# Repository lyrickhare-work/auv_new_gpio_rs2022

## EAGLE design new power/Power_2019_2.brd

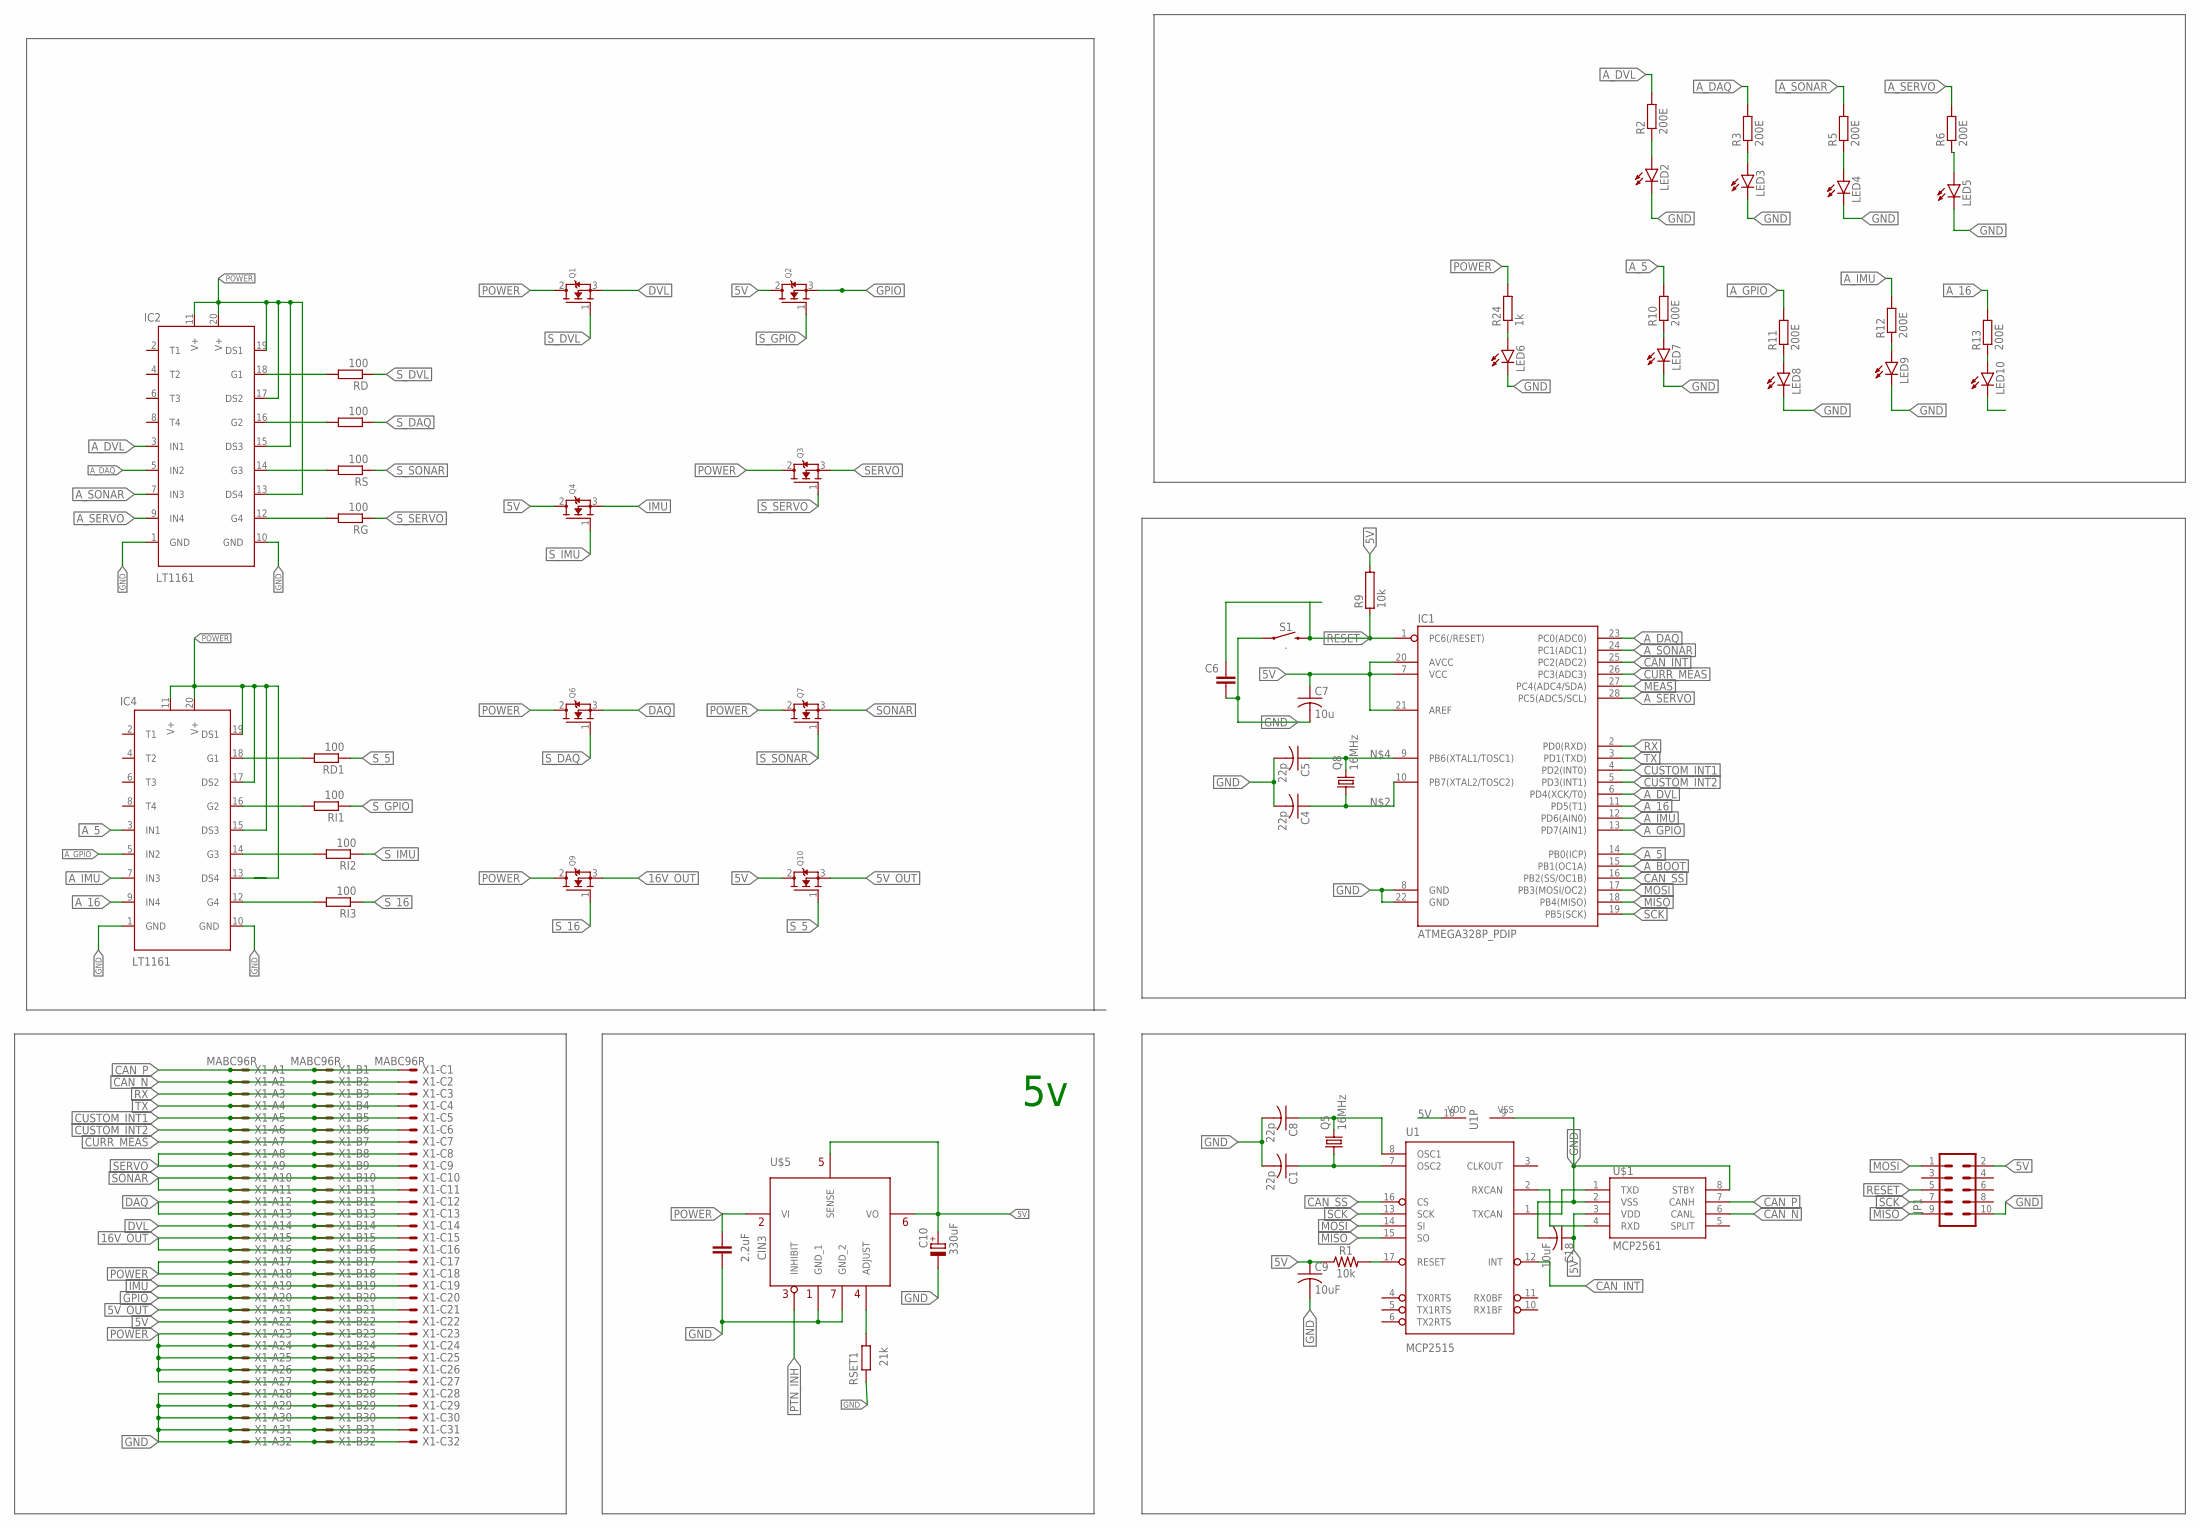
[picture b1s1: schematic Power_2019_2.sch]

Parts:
C1, C4, C5, C8: 22p; C025-024X044
C6: C-EU025-050X050; C025-050X050
C7: 10u; C025-050X050
C9, C18: 10uF; C025-050X050
C10: 330uF; E2,5-5
CIN3: 2.2uF; C0805
IC1: ATMEGA328P_PDIP; DIL28-3
IC2, IC4: LT1161; ROBOSUB_LINEAR-TECHNOLOGY_LT1161_QUAD-HIGH-SIDE-MOSFET-DRIV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
JP1: CONN_05X2SHD; 2X5-SHROUDED
LED2, LED3, LED4, LED5, LED6, LED7, LED8, LED9, LED10: LEDCHIPLED_0805; CHIPLED_0805
Q1, Q2, Q3, Q4, Q6, Q7, Q9, Q10: MOSFET-NGDS_TO220V; TO220V
Q5, Q8: 16MHz; HC49/S
R1: 10k; AXIAL-0.3
R2, R3, R5, R6, R10, R11, R12, R13: 200E; M0805
R9: 10k; RS1/4
R24: 1k; M0805
RD, RD1: 100; M0805
RG: 100; M0805
RI, RI1, RI2, RI3: 100; M0805
RS: 100; M0805
RSET1: 21k; M0805
S1: .; TACTILE_SWITCH_PTH_6.0MM
U1: MCP2515; DIP18
U$1: MCP2561; DIP08
U$5: PTN78060WAH
X1: MABC96R

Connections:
5V: C7.1, C9.1, C10.+, C18.1, IC1.7 (VCC), IC1.20 (AVCC), IC1.21 (AREF), JP1.2, Q2.2 (D), Q4.2 (D), Q10.2 (D), R1.P$1 (1), R9.2, U1.18 (VDD), U$1.3 (VDD), U$5.5 (SENSE), U$5.6 (VO), X1.A22, X1.B22, X1.C22
5V_OUT: Q10.3 (S), X1.A21, X1.B21, X1.C21
16V_OUT: Q9.3 (S), X1.A15, X1.A16, X1.B15, X1.B16, X1.C15, X1.C16
A_5: IC1.14 (PB0(ICP)), IC4.3 (IN1), R10.2
A_16: IC1.11 (PD5(T1)), IC4.9 (IN4), R13.2
A_BOOT: IC1.15 (PB1(OC1A))
A_DAQ: IC1.23 (PC0(ADC0)), IC2.5 (IN2), R3.2
A_DVL: IC1.6 (PD4(XCK/T0)), IC2.3 (IN1), R2.2
A_GPIO: IC1.13 (PD7(AIN1)), IC4.5 (IN2), R11.2
A_IMU: IC1.12 (PD6(AIN0)), IC4.7 (IN3), R12.2
A_SERVO: IC1.28 (PC5(ADC5/SCL)), IC2.9 (IN4), R6.2
A_SONAR: IC1.24 (PC1(ADC1)), IC2.7 (IN3), R5.2
CAN_INT: IC1.25 (PC2(ADC2)), U1.12 (INT)
CAN_N: U$1.6 (CANL), X1.A2, X1.B2, X1.C2
CAN_P: U$1.7 (CANH), X1.A1, X1.B1, X1.C1
CAN_SS: IC1.16 (PB2(SS/OC1B)), U1.16 (CS)
CURR_MEAS: IC1.26 (PC3(ADC3)), X1.A7, X1.B7, X1.C7
CUSTOM_INT1: IC1.4 (PD2(INT0)), X1.A5, X1.B5, X1.C5
CUSTOM_INT2: IC1.5 (PD3(INT1)), X1.A6, X1.B6, X1.C6
D: IC2.12 (G4), RG.2
DAQ: Q6.3 (S), X1.A12, X1.A13, X1.B12, X1.B13, X1.C12, X1.C13
DVL: Q1.3 (S), X1.A14, X1.B14, X1.C14
G: IC2.18 (G1), RD.2
G1: IC4.18 (G1), RD1.2
GND: C1.2, C4.2, C5.2, C6.2, C7.2, C8.2, C9.2, C10.-, C18.2, CIN3.1, IC1.8 (GND), IC1.22 (GND), IC2.1 (GND), IC2.10 (GND), IC4.1 (GND), IC4.10 (GND), JP1.10, LED2.C, LED3.C, LED4.C, LED5.C, LED6.C, LED7.C, LED8.C, LED9.C, LED10.C, RSET1.2, S1.1, U1.9 (VSS), U$1.2 (VSS), U$1.8 (STBY), U$5.1 (GND_1), U$5.7 (GND_2), X1.A28, X1.A29, X1.A30, X1.A31, X1.A32, X1.B28, X1.B29, X1.B30, X1.B31, X1.B32, X1.C28, X1.C29, X1.C30, X1.C31, X1.C32
GPIO: Q2.3 (S), X1.A20, X1.B20, X1.C20
I: IC2.14 (G3), RS.2
IMU: Q4.3 (S), X1.A19, X1.B19, X1.C19
MEAS: IC1.27 (PC4(ADC4/SDA))
MISO: IC1.18 (PB4(MISO)), JP1.9, U1.15 (SO)
MOSI: IC1.17 (PB3(MOSI/OC2)), JP1.1, U1.14 (SI)
unnamed: LED2.A, R2.1
unnamed: C4.1, IC1.10 (PB7(XTAL2/TOSC2)), Q8.1
unnamed: U1.1 (TXCAN), U$1.1 (TXD)
unnamed: C5.1, IC1.9 (PB6(XTAL1/TOSC1)), Q8.2
unnamed: LED3.A, R3.1
unnamed: U1.2 (RXCAN), U$1.4 (RXD)
unnamed: R1.P$2 (2), U1.17 (RESET)
unnamed: C1.1, Q5.1, U1.7 (OSC2)
unnamed: C8.1, Q5.2, U1.8 (OSC1)
unnamed: RSET1.1, U$5.4 (ADJUST)
unnamed: LED4.A, R5.1
unnamed: LED5.A, R6.1
unnamed: LED7.A, R10.1
unnamed: LED6.A, R24.1
unnamed: LED8.A, R11.1
unnamed: LED9.A, R12.1
unnamed: LED10.A, R13.1
unnamed: IC4.14 (G3), RI2.2
unnamed: IC4.12 (G4), RI3.2
POWER: CIN3.2, IC2.11 (V+), IC2.13 (DS4), IC2.15 (DS3), IC2.17 (DS2), IC2.19 (DS1), IC2.20 (V+), IC4.11 (V+), IC4.13 (DS4), IC4.15 (DS3), IC4.17 (DS2), IC4.19 (DS1), IC4.20 (V+), Q1.2 (D), Q3.2 (D), Q6.2 (D), Q7.2 (D), Q9.2 (D), R24.2, U$5.2 (VI), X1.A17, X1.A18, X1.A23, X1.A24, X1.A25, X1.A26, X1.A27, X1.B17, X1.B18, X1.B23, X1.B24, X1.B25, X1.B26, X1.B27, X1.C17, X1.C18, X1.C23, X1.C24, X1.C25, X1.C26, X1.C27
PTN_INH: U$5.3 (INHIBIT)
RESET: C6.1, IC1.1 (PC6(/RESET)), JP1.5, R9.1, S1.3 (2)
RX: IC1.2 (PD0(RXD)), X1.A3, X1.B3, X1.C3
S: IC2.16 (G2), RI.2
S1: IC4.16 (G2), RI1.2
SCK: IC1.19 (PB5(SCK)), JP1.7, U1.13 (SCK)
SERVO: Q3.3 (S), X1.A8, X1.A9, X1.B8, X1.B9, X1.C8, X1.C9
SONAR: Q7.3 (S), X1.A10, X1.A11, X1.B10, X1.B11, X1.C10, X1.C11
S_5: Q10.1 (G), RD1.1
S_16: Q9.1 (G), RI3.1
S_DAQ: Q6.1 (G), RI.1
S_DVL: Q1.1 (G), RD.1
S_GPIO: Q2.1 (G), RI1.1
S_IMU: Q4.1 (G), RI2.1
S_SERVO: Q3.1 (G), RG.1
S_SONAR: Q7.1 (G), RS.1
TX: IC1.3 (PD1(TXD)), X1.A4, X1.B4, X1.C4

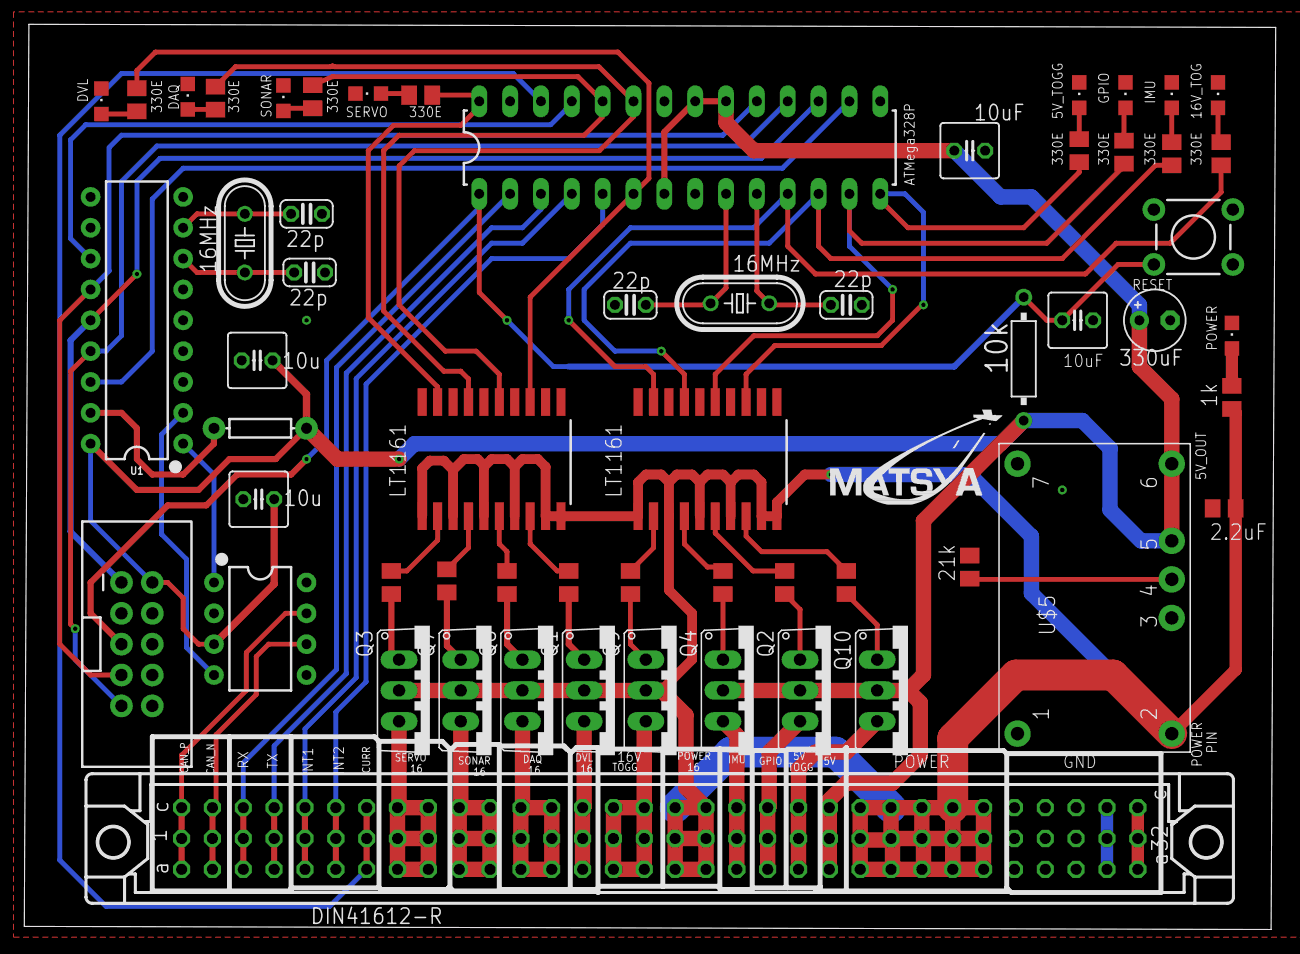
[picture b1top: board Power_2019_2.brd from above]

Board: 2 copper layers, 103.0 x 74.5 mm, 58 parts (0 on the bottom side), 65 nets.

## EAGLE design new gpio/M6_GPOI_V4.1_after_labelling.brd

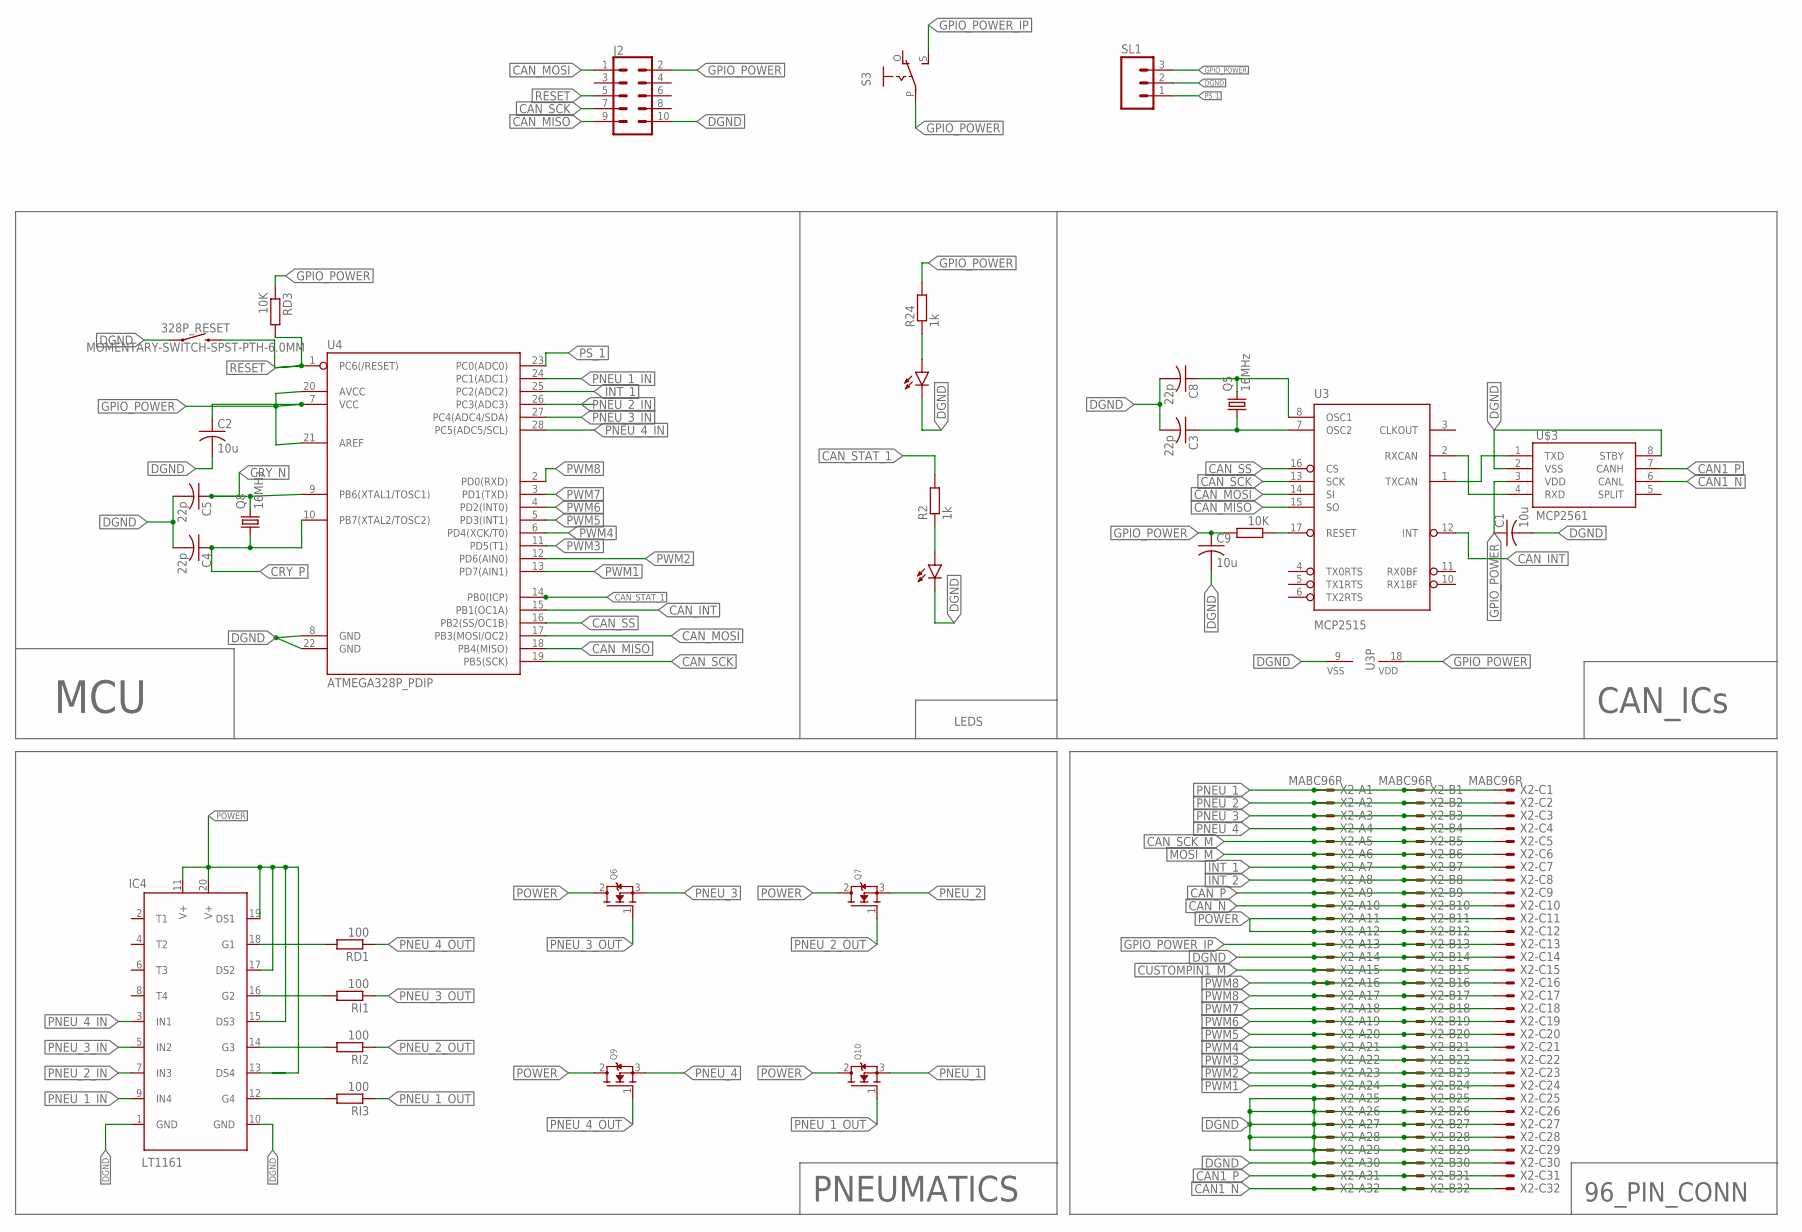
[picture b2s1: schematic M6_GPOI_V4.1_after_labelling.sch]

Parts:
328P_RESET: MOMENTARY-SWITCH-SPST-PTH-6.0MM; TACTILE_SWITCH_PTH_6.0MM
C1, C2, C9: 10u; C025-050X050
C3, C4, C5, C8: 22p; C025-024X044
IC4: LT1161; ROBOSUB_LINEAR-TECHNOLOGY_LT1161_QUAD-HIGH-SIDE-MOSFET-DRIV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
J2: CONN_05X2SHD; 2X5-SHROUDED
PWR, PWR1: LED5MM
Q5, Q8: 16MHz; HC49/S
Q6, Q7, Q9, Q10: MOSFET-NGDS_TO220V; TO220V
R2, R24: 1k; M0805
RD1: 100; M0805
RD2, RD3: 10K; M0805
RI1, RI2, RI3: 100; M0805
S3: EG1218S; EG1218
SL1: MA03; 03P
U3: MCP2515; DIP18
U4: ATMEGA328P_PDIP; DIL28-3
U$3: MCP2561; DIP08
X2: MABC96R

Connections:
CAN1_N: U$3.6 (CANL), X2.A32, X2.B32, X2.C32
CAN1_P: U$3.7 (CANH), X2.A31, X2.B31, X2.C31
CAN_INT: U3.12 (INT), U4.15 (PB1(OC1A))
CAN_MISO: J2.9, U3.15 (SO), U4.18 (PB4(MISO))
CAN_MOSI: J2.1, U3.14 (SI), U4.17 (PB3(MOSI/OC2))
CAN_N: X2.A10, X2.B10, X2.C10
CAN_P: X2.A9, X2.B9, X2.C9
CAN_SCK: J2.7, U3.13 (SCK), U4.19 (PB5(SCK))
CAN_SCK_M: X2.A5, X2.B5, X2.C5
CAN_SS: U3.16 (CS), U4.16 (PB2(SS/OC1B))
CAN_STAT_1: R2.2, U4.14 (PB0(ICP))
CRY_N: C5.1, Q8.2, U4.9 (PB6(XTAL1/TOSC1))
CRY_P: C4.1, Q8.1, U4.10 (PB7(XTAL2/TOSC2))
CUSTOMPIN1_M: X2.A15, X2.B15, X2.C15
C_N: C8.1, Q5.2, U3.8 (OSC1)
C_P: C3.1, Q5.1, U3.7 (OSC2)
DGND: 328P_RESET.1, C1.2, C2.2, C3.2, C4.2, C5.2, C8.2, C9.2, IC4.1 (GND), IC4.10 (GND), J2.10, PWR.K (C), PWR1.K (C), SL1.2, U3.9 (VSS), U4.8 (GND), U4.22 (GND), U$3.2 (VSS), U$3.8 (STBY), X2.A14, X2.A25, X2.A26, X2.A27, X2.A28, X2.A29, X2.A30, X2.B14, X2.B25, X2.B26, X2.B27, X2.B28, X2.B29, X2.B30, X2.C14, X2.C25, X2.C26, X2.C27, X2.C28, X2.C29, X2.C30
G1: IC4.18 (G1), RD1.2
GPIO_POWER: C1.1, C2.1, C9.1, J2.2, R24.2, RD2.2, RD3.1, S3.P, SL1.3, U3.18 (VDD), U4.7 (VCC), U4.20 (AVCC), U4.21 (AREF), U$3.3 (VDD)
GPIO_POWER_IP: S3.S, X2.A13, X2.B13, X2.C13
INT_1: U4.25 (PC2(ADC2)), X2.A7, X2.B7, X2.C7
INT_2: X2.A8, X2.B8, X2.C8
MOSI_M: X2.A6, X2.B6, X2.C6
unnamed: PWR1.A, R2.1
unnamed: U3.1 (TXCAN), U$3.1 (TXD)
unnamed: U3.2 (RXCAN), U$3.4 (RXD)
unnamed: RD2.1, U3.17 (RESET)
unnamed: IC4.14 (G3), RI2.2
unnamed: IC4.12 (G4), RI3.2
unnamed: PWR.A, R24.1
PNEU_1: Q10.3 (S), X2.A1, X2.B1, X2.C1
PNEU_1_IN: IC4.9 (IN4), U4.24 (PC1(ADC1))
PNEU_1_OUT: Q10.1 (G), RI3.1
PNEU_2: Q7.3 (S), X2.A2, X2.B2, X2.C2
PNEU_2_IN: IC4.7 (IN3), U4.26 (PC3(ADC3))
PNEU_2_OUT: Q7.1 (G), RI2.1
PNEU_3: Q6.3 (S), X2.A3, X2.B3, X2.C3
PNEU_3_IN: IC4.5 (IN2), U4.27 (PC4(ADC4/SDA))
PNEU_3_OUT: Q6.1 (G), RI1.1
PNEU_4: Q9.3 (S), X2.A4, X2.B4, X2.C4
PNEU_4_IN: IC4.3 (IN1), U4.28 (PC5(ADC5/SCL))
PNEU_4_OUT: Q9.1 (G), RD1.1
POWER: IC4.11 (V+), IC4.13 (DS4), IC4.15 (DS3), IC4.17 (DS2), IC4.19 (DS1), IC4.20 (V+), Q6.2 (D), Q7.2 (D), Q9.2 (D), Q10.2 (D), X2.A11, X2.A12, X2.B11, X2.B12, X2.C11, X2.C12
PS_1: SL1.1, U4.23 (PC0(ADC0))
PWM1: U4.13 (PD7(AIN1)), X2.A24, X2.B24, X2.C24
PWM2: U4.12 (PD6(AIN0)), X2.A23, X2.B23, X2.C23
PWM3: U4.11 (PD5(T1)), X2.A22, X2.B22, X2.C22
PWM4: U4.6 (PD4(XCK/T0)), X2.A21, X2.B21, X2.C21
PWM5: U4.5 (PD3(INT1)), X2.A20, X2.B20, X2.C20
PWM6: U4.4 (PD2(INT0)), X2.A19, X2.B19, X2.C19
PWM7: U4.3 (PD1(TXD)), X2.A18, X2.B18, X2.C18
PWM8: U4.2 (PD0(RXD)), X2.A16, X2.A17, X2.B16, X2.B17, X2.C16, X2.C17
RESET: 328P_RESET.3 (2), J2.5, RD3.2, U4.1 (PC6(/RESET))
S1: IC4.16 (G2), RI1.2

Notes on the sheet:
PNEUMATICS
96_PIN_CONN
CAN_ICs
MCU
LEDS

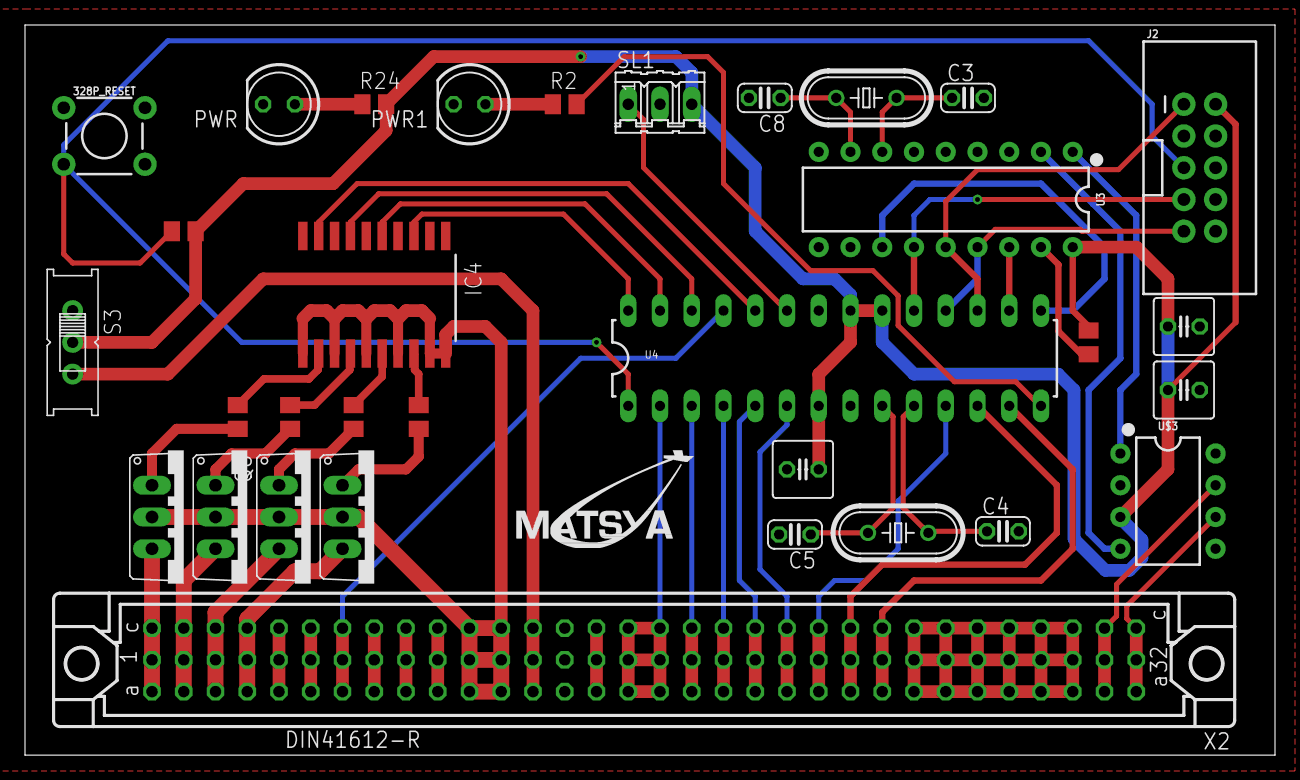
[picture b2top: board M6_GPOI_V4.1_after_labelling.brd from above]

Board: 2 copper layers, 100.0 x 58.4 mm, 32 parts (0 on the bottom side), 54 nets.

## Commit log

2022-06-01 ITER1 drc check not labelled
2022-06-01 updated with dimensions
2022-06-02 some random chages
2022-06-05 gpio with nobi's changes
2022-06-05 new power brd
    sch modified, brd placed and little routed
2022-06-06 power board without labelling
2022-06-08 FINAL BY LK WITHOUT LABELLING
2022-06-08 power labelling done
2022-06-08 power labelled
2022-06-08 GPIO LABELLED
2022-06-08 pics of boards added
2022-06-08 gpio mosfet
2022-06-08 MORE gpio labelling
2022-06-08 POWER BIT CHANGE1
2022-06-09 final from lk without labelling
2022-06-09 power 90 deg

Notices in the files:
parts and their libraries:
SparkFun-Switches: Licensing: Creative Commons ShareAlike 4.0 International - https://creativecommons.org/licenses/by-sa/4.0
